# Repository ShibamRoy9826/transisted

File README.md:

# Transisted ⚡

## Description 🖋️
Its a simple project that I made to learn about transistors!

I used [Pikachu](https://en.wikipedia.org/wiki/Pikachu) for the design of the board, cause it looks kawaii to me:) (To whom does it not look cute?)

It primarily consists of 3 LEDs, when the first push button is pressed, the first 2 LEDs (cheeks of pikachu) glow up.
The second button is conditional, and only works when the first one is activated.

Moreover, the second LED (at the tail of pikachu) brightness can be controlled, as it passes through a potentiometer.

## Simulations 📽️

Some simulations if you want to try out my circuit!

*Tinkercad* - [here](https://www.tinkercad.com/things/52eL0hILRMp-transisted?sharecode=undefined)
*CircuitJS* - [here](https://tinyurl.com/265tfk4g)

## Screenshots 📷

### 3D front

### 3D back

### Schematic

### PCB

## BOM

| Part Name  | Quantity |
| ------------- | ------------- |
| Coin-sized Battery Holder  | x1  |
| LEDs  | x3  |
| 220 ohm resistor | x1 |
| Potentiometer | x1 |
| NPN transistors | x2 |
| 6mm tactile push buttons | x2 |

## Credits 💖

Thank you Hackclub for providing such great learning resources! This project was made during an event called [solder](https://solder.hackclub.com) at Hackclub, where teenagers build circuits and learn about electronics!
Special thanks to [@cyao](https://github.com/cheyao) and [@acon](https://github.com/acornitum) for organising this event and writing such a nice guide for beginners 💖

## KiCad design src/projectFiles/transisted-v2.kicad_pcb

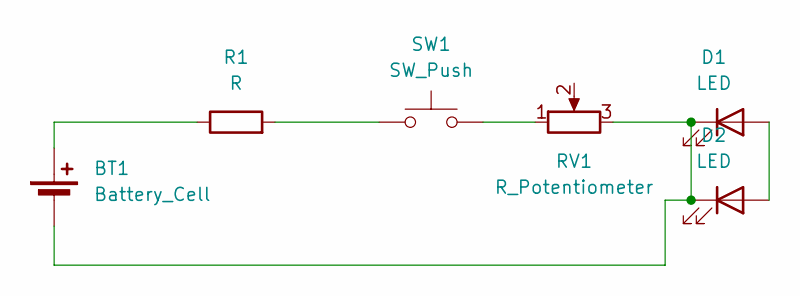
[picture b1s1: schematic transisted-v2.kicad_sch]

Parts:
BT1: Battery_Cell; BatteryHolder_Keystone_3034_1x20mm
D1, D2: LED; LED_D5.0mm
R1: R; R_Axial_DIN0207_L6.3mm_D2.5mm_P7.62mm_Horizontal
RV1: R_Potentiometer; Potentiometer_Vishay_T73YP_Vertical
SW1: SW_Push; SW_PUSH_6mm

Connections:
unnamed: BT1.1 (+), R1.1
unnamed: BT1.2 (-), D1.1 (K), D2.1 (K), RV1.3
unnamed: D1.2 (A), D2.2 (A)
unnamed: R1.2, SW1.1
unnamed: RV1.1, SW1.2

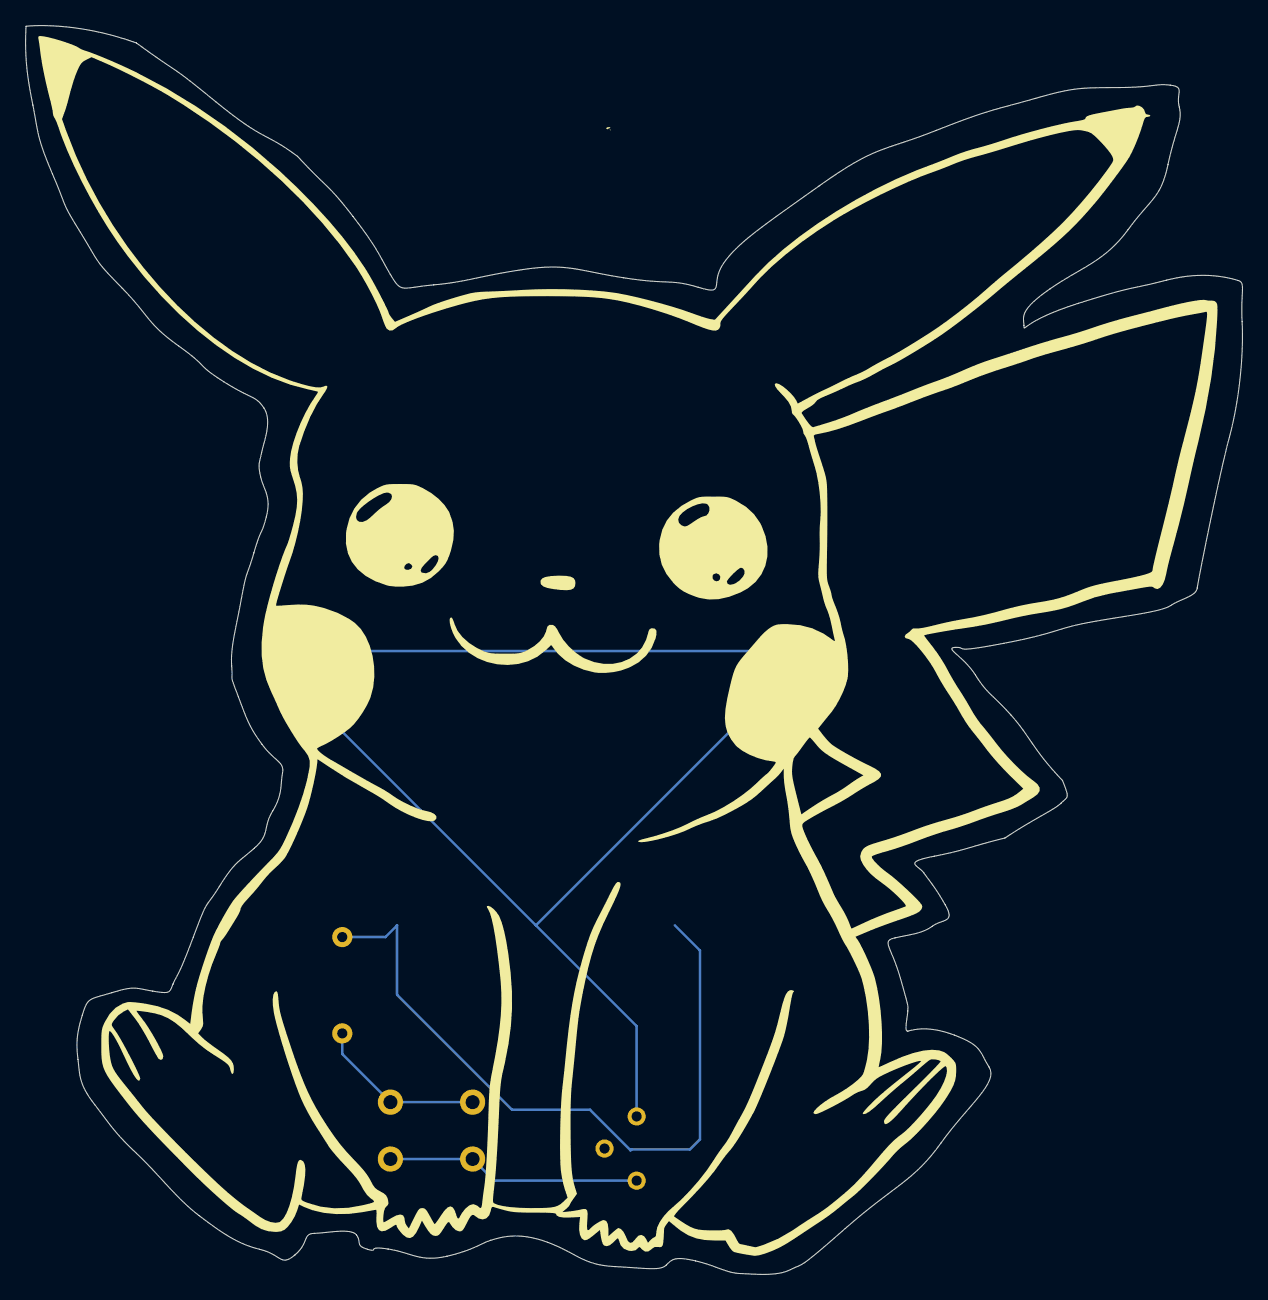
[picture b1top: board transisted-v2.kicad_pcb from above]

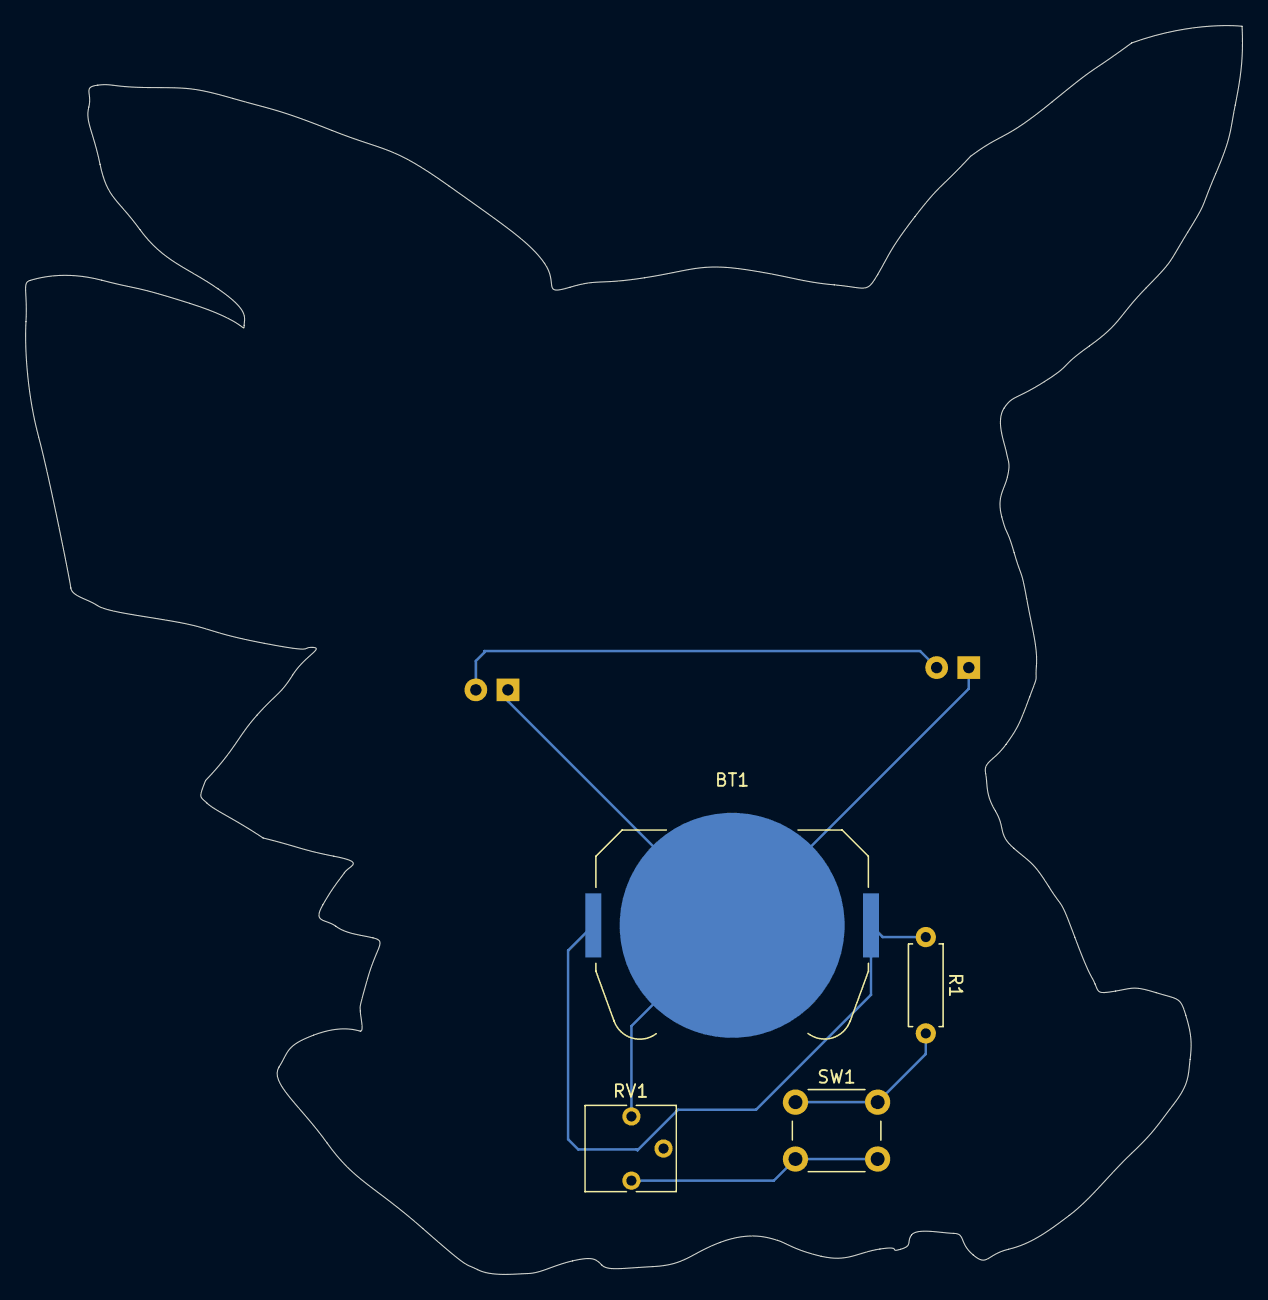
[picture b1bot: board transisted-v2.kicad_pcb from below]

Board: 2 copper layers, 96.3 x 98.8 mm, 6 parts (4 on the bottom side), 5 nets.

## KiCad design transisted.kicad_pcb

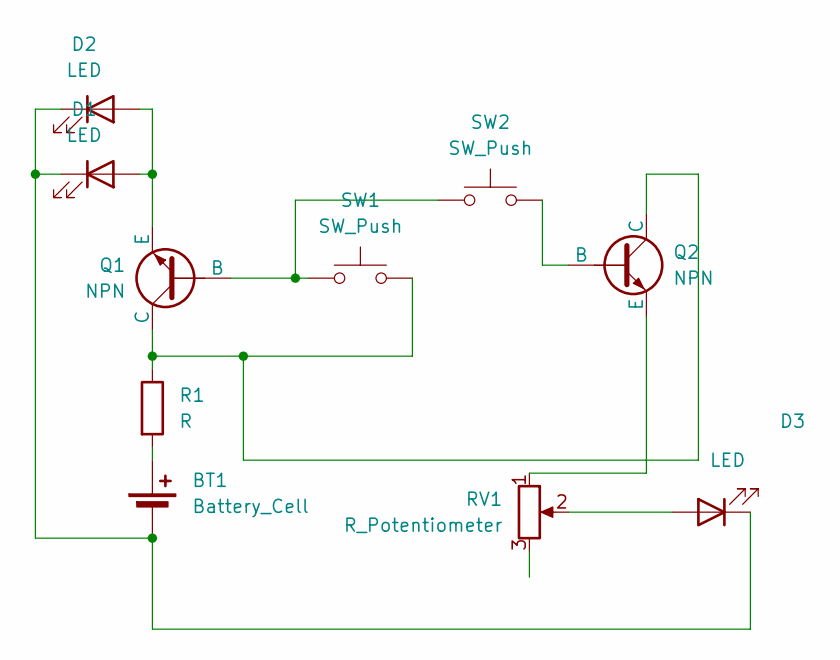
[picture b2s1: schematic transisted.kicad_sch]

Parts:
BT1: Battery_Cell; BatteryHolder_Keystone_3034_1x20mm
D1, D2, D3: LED; LED_D5.0mm
Q1, Q2: NPN; TO-92L_HandSolder
R1: R; R_Axial_DIN0207_L6.3mm_D2.5mm_P7.62mm_Horizontal
RV1: R_Potentiometer; Potentiometer_Vishay_T73YP_Vertical
SW1, SW2: SW_Push; SW_PUSH_6mm

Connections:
unnamed: BT1.1 (+), R1.2
unnamed: BT1.2 (-), D1.1 (K), D2.1 (K), D3.1 (K)
unnamed: D1.2 (A), D2.2 (A), Q1.3 (E)
unnamed: D3.2 (A), RV1.2
unnamed: Q1.2 (B), SW1.1, SW2.1
unnamed: Q1.1 (C), Q2.1 (C), R1.1, SW1.2
unnamed: Q2.2 (B), SW2.2
unnamed: Q2.3 (E), RV1.1

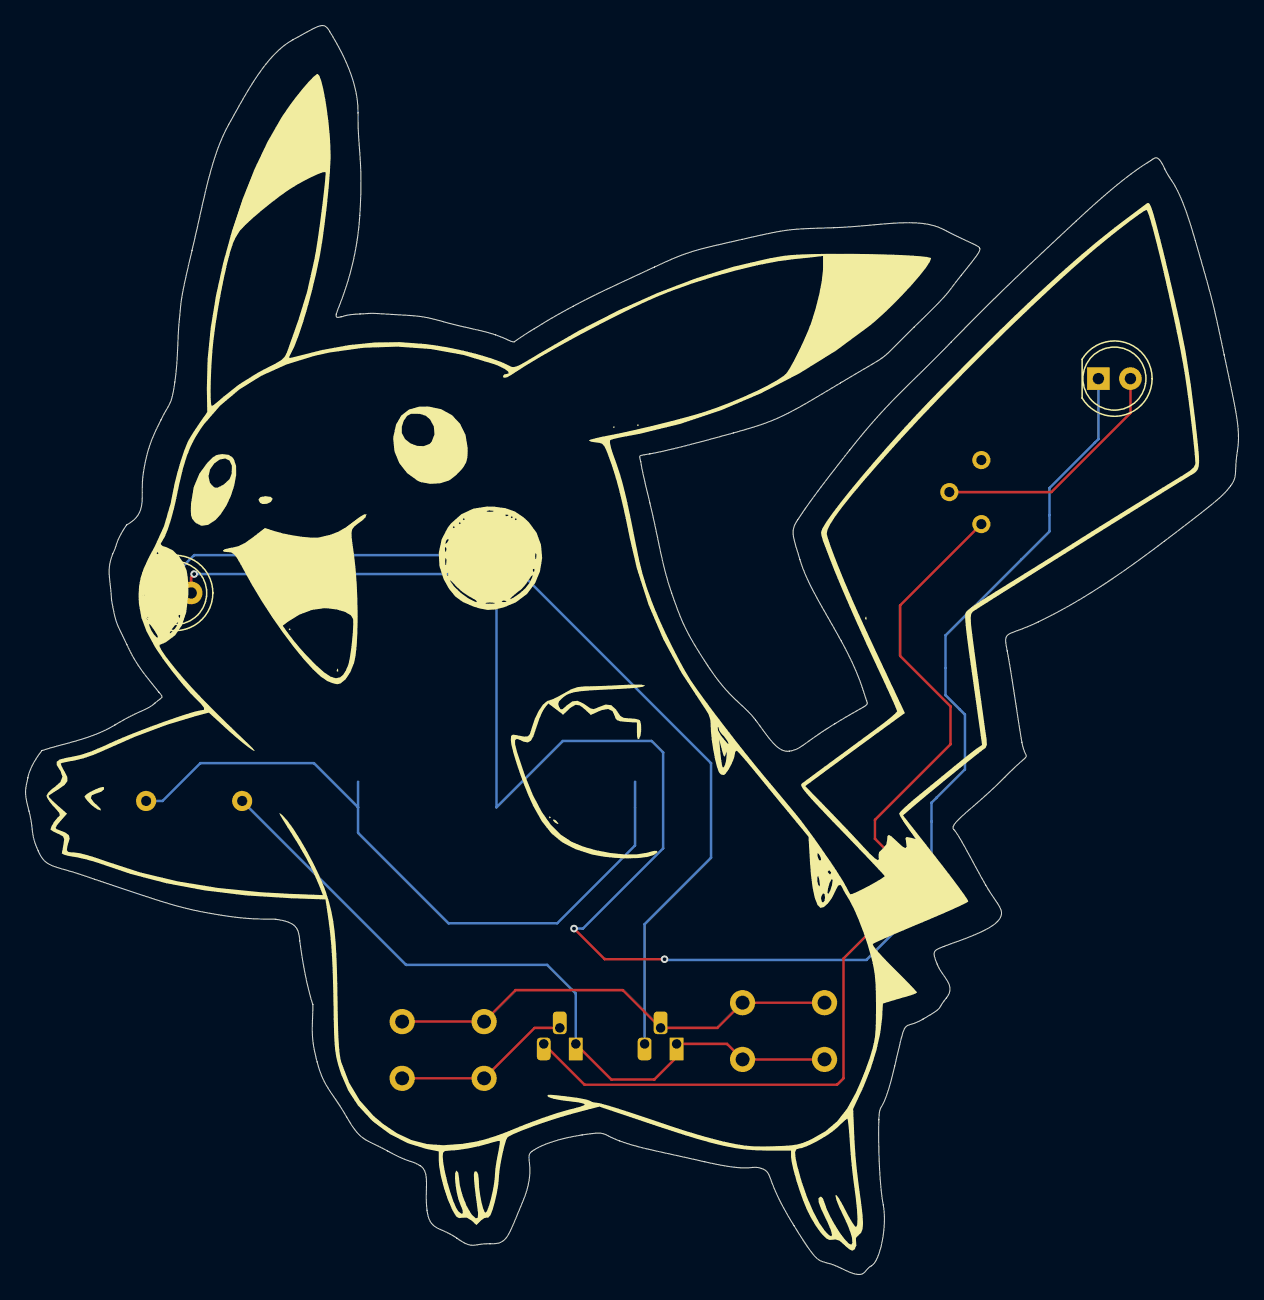
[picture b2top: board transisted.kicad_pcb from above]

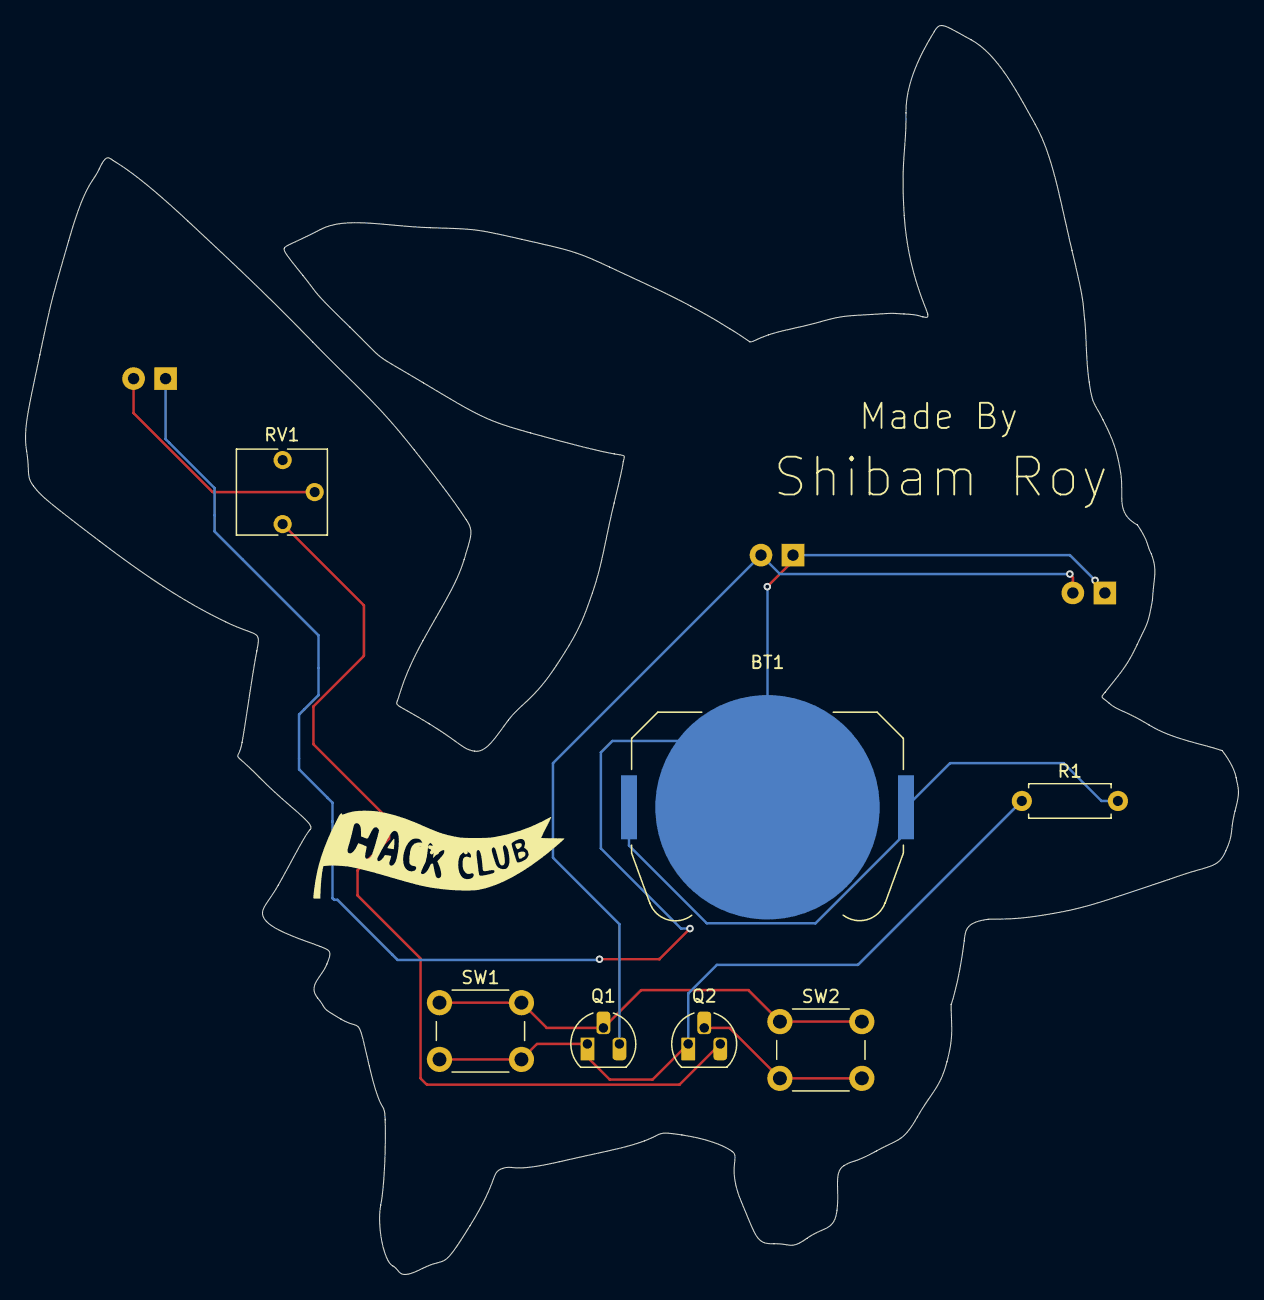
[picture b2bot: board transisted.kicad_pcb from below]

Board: 2 copper layers, 96.2 x 99.1 mm, 10 parts (7 on the bottom side), 8 nets.

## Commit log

2025-05-13 Added all necessary files
2025-05-13 removed unnecessary files
2025-05-13 Added screenshots and readme
2025-05-13 Update README.md
    Added BOM and improved readme
2025-05-13 Removed an unnecessary trace
2025-05-23 Initial commit of v2
